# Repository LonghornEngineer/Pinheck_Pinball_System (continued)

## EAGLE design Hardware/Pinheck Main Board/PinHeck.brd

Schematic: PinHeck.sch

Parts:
3.3V, 5V, 12V, 50V: TEST_POINT_SINGLE_ROUND_100MIL; 100MIL_TP
AUDIO: SJ1-3533NS
AUX_PWR: 26-64-4040
BACK_OUT: TEST_POINT_SINGLE_ROUND_100MIL; 100MIL_TP
BATT1: 1066
BOARD_POWER_IN: 26-64-4040; 26-64-4040(KEYPIN2)
C1, C2, C3, C4, C5, C6, C7, C9, C11, C12, C20, C21, C22, C23, C24, C25, C26, C28, C30, C31, C32, C33, C37, C38, C41, C42, C45, C46, C47, C53, C54, C55, C56, C57, C62, C63, C64, C65: .1uF; 0805
C8, C36, C40, C44, C48, C52: 1uF; 0805
C10, C35, C39, C43, C51: 10uF; 1206
C13, C14: 30pF; 0805
C15, C16, C17, C18, C19: MF-CAP-12.5MM-1000uF; CP12.5MM
C27, C34, C49, C50: EEE-1VA101XP; 6.3MM_CAP_SMD
C29: MF-CAP-12.5MM-1000uF; CP6.3MM
C58, C60: 0.1uF; 0805
C59: 2.2nF; 0805
C61: 5.6nF; 0805
CABINET_I/O: 26-64-4120
CAB_RGB: 26-64-4110; 26-64-4110(KEYPIN3)
COIN_OUT: TEST_POINT_SINGLE_ROUND_100MIL; 100MIL_TP
D1: BAV99W,115; SOT-323
D2: CGRM4001-HF; SOD-123
D3: SMBJ6.0CA; SMBJ
D4: SMBJ15CA; SMBJ
D5, D6, D7, D8, D9, D10, D11: LO Q976-PS-25; LED0603
DMD_1, DMD_3, DMD_5, DMD_7, DMD_9, DMD_11, DMD_13: TEST_POINT_SINGLE_ROUND_100MIL; 100MIL_TP
DMD_CON: 5103308-2
DMD_PWR: CON_01X03_26-64-4040_(KEYPIN1); 26-64-4040(KEYPIN1)
DOOR_OUT: TEST_POINT_SINGLE_ROUND_100MIL; 100MIL_TP
ENTER_OUT: TEST_POINT_SINGLE_ROUND_100MIL; 100MIL_TP
EXT_RGB_CLK: TEST_POINT_SINGLE_ROUND_100MIL; 100MIL_TP
EXT_RGB_DATA: TEST_POINT_SINGLE_ROUND_100MIL; 100MIL_TP
F1, F2, F3, F4, F5, F6, F7: 4628
FID1, FID2, FID3: FIDUCIAL_100MIL
FID4, FID5: FIDUCIAL_0.5MM
FLASHER: 26-64-4020
GI0, GI1, GI2, GI3, GI4, GI5, GI6, GI7, GI8, GI9, GI10, GI11, GI12, GI13, GI14, GI15: TIP102; TO-220AB
GI15_: TEST_POINT_SINGLE_ROUND_100MIL; 100MIL_TP
GI_0: 26-64-4100; 26-64-4100(KEYPIN9)
GI_1: 26-64-4100; 26-64-4100(KEYPIN10)
GI_R_0, GI_R_1, GI_R_2, GI_R_3, GI_R_4, GI_R_5, GI_R_6, GI_R_7, GI_R_8, GI_R_9, GI_R_10, GI_R_11, GI_R_12, GI_R_13, GI_R_14: TEST_POINT_SINGLE_ROUND_100MIL; 100MIL_TP
GND: TEST_POINT_SINGLE_ROUND_100MIL; 100MIL_TP
H2, H3, H4, H11, H19, H21, H22, H23, H24, H26, H27, H28, H30, H31, H32, H33, H34: MOUNT_HOLE150MIL; MOUNT_HOLE_150MIL
IC2: PIC32MX795F512L-80I/PT; TQ100-PT
IC3, IC4: CD74HCT244E; DIL20
IC5: ULN2803A; DIL18
KNOCKER: 26-64-4020
LIGHT_COL: 26-64-4100; 26-64-4100(KEYPIN2)
LIGHT_C_0, LIGHT_C_1, LIGHT_C_2, LIGHT_C_3, LIGHT_C_4, LIGHT_C_5, LIGHT_C_6, LIGHT_C_7: TEST_POINT_SINGLE_ROUND_100MIL; 100MIL_TP
LIGHT_ROW: 26-64-4100; 26-64-4100(KEYPIN3)
LIGHT_R_0, LIGHT_R_1, LIGHT_R_2, LIGHT_R_3, LIGHT_R_4, LIGHT_R_5, LIGHT_R_6, LIGHT_R_7: TEST_POINT_SINGLE_ROUND_100MIL; 100MIL_TP
LOGO1: SPOOKY_LOGOSPOOKY_LOGO; SPOOKY_LOGO
L_FLIP_OUT: TEST_POINT_SINGLE_ROUND_100MIL; 100MIL_TP
OPTO_1, OPTO_2, OPTO_3, OPTO_4, OPTO_5, OPTO_6, OPTO_7: 26-64-4040
OPTO_1_, OPTO_2_, OPTO_3_, OPTO_4_, OPTO_5_, OPTO_6_, OPTO_7_: TEST_POINT_SINGLE_ROUND_100MIL; 100MIL_TP
PHABULOUS: 26-64-4050; 2.54MM_01X20_PIN_HEADER
PIC32_TC: TC2030-FTDI-TTL-232R; TC2030
PIC32_UART: CON_01X06_2.54MM_PIN_HEADER; 2.54MM_01X06_PIN_HEADER
PICKIT3: CON_01X06_2.54MM_PIN_HEADER; 2.54MM_01X06_PIN_HEADER
PICKIT3_TC: TC2030-PKT-NL; TC2030
PIC_PROGRAM: TACT_6MM; TACT6MM
PIC_RESET: TACT_6MM; TACT6MM
PROP_ACT: LG R971-KN-1; LED_0805
PROP_AUX0, PROP_AUX1: TEST_POINT_SINGLE_ROUND_100MIL; 100MIL_TP
PROP_CONFIG: TACT_6MM; TACT6MM
PROP_RESET: TACT_6MM; TACT6MM
PROP_TC: TC2030-FTDI-TTL-232R; TC2030
PROP_UART: CON_01X06_2.54MM_PIN_HEADER; 2.54MM_01X06_PIN_HEADER
PSU_PWR: LG R971-KN-1; LED_0805
R1, R4, R16, R17, R18, R19, R20, R21, R22, R23, R24, R25, R35, R36, R37, R38, R39, R40, R41, R42, R43, R44, R45, R46, R47, R48, R49, R50, R51, R52, R53, R54, R55, R56, R57, R58, R59, R60, R61, R62, R63, R64, R65, R66, R67, R68, R69, R70, R71, R72, R73, R74, R75, R76, R77, R78, R79, R80, R81, R82, R83, R85, R87, R89, R91, R93, R95, R97, R115, R119, R120, R121, R122, R123, R124, R133, R135, R137, R176: 10K; 0805
R2, R6, R9, R11, R27, R29, R33: 2K; 0805
R3, R136: 0; 0805
R5, R7, R10, R15, R28, R31, R138: 1K; 0805
R8, R139, R140, R141, R142, R143, R144, R145: 200; 0805
R12, R13, R14: 50; 0805
R26, R148, R149, R150, R151, R152, R153, R154, R155, R156: 100; 0805
R30, R84, R86, R88, R90, R92, R94, R96, R98, R99, R100, R101, R102, R103, R104, R105, R106, R107, R108, R109, R110, R111, R112, R113, R114, R116, R117, R118, R125, R126, R127, R128, R129, R130, R131, R132: 360; 0805
R32, R34: 4.7K; 0805
R134: 25K; 0805
R146: 130K; 0805
R147, R158: 1M; 0805
R157: 110K; 0805
R159, R161, R162: 180; 0805
R160: 680; 0805
R163, R164, R165: CRCW25125K60JNEG; 2512
RGB_0, RGB_1, RGB_2, RGB_3, RGB_4, RGB_5: RFP12N10L; TO-220AB
RGB_BOUT_L: TEST_POINT_SINGLE_ROUND_100MIL; 100MIL_TP
RGB_BOUT_R: TEST_POINT_SINGLE_ROUND_100MIL; 100MIL_TP
RGB_COM_OUT: 26-64-4080; 26-64-4080(KEYPIN2)
RGB_GOUT_L: TEST_POINT_SINGLE_ROUND_100MIL; 100MIL_TP
RGB_GOUT_R: TEST_POINT_SINGLE_ROUND_100MIL; 100MIL_TP
RGB_ROUT_L: TEST_POINT_SINGLE_ROUND_100MIL; 100MIL_TP
RGB_ROUT_R: TEST_POINT_SINGLE_ROUND_100MIL; 100MIL_TP
R_FLIP_OUT: TEST_POINT_SINGLE_ROUND_100MIL; 100MIL_TP
SD0: SD-RSMT-2-MQ
SD_CS: TEST_POINT_SINGLE_ROUND_100MIL; 100MIL_TP
SD_DI: TEST_POINT_SINGLE_ROUND_100MIL; 100MIL_TP
SD_DO: TEST_POINT_SINGLE_ROUND_100MIL; 100MIL_TP
SD_SCLK: TEST_POINT_SINGLE_ROUND_100MIL; 100MIL_TP
SERVO_0, SERVO_1, SERVO_2, SERVO_3, SERVO_4: 640454-3
SERVO_0_, SERVO_1_, SERVO_2_, SERVO_3_, SERVO_4_: TEST_POINT_SINGLE_ROUND_100MIL; 100MIL_TP
SHAKER: 26-64-4020
SOCKET1, SOCKET2: 820-AG11D-ESL-LF; 20PIN_DIP_SOCKET
SOCKET3, SOCKET5: 808-AG11D-ESL-LF; 8PIN_DIP_SOCKET
SOCKET4: 818-AG11D-ESL-LF; 18PIN_DIP_SOCKET
SOLENOID_POWER_IN: 26-64-4040; 26-64-4040(KEYPIN3)
SOL_0, SOL_1, SOL_2, SOL_3, SOL_4, SOL_5, SOL_6, SOL_7, SOL_8, SOL_9, SOL_10, SOL_11, SOL_12, SOL_13, SOL_14, SOL_15, SOL_16, SOL_17, SOL_18, SOL_19, SOL_20, SOL_21, SOL_22, SOL_23: IRL530PBF; TO-220AB
SOL_BANK_0: 26-64-4100; 26-64-4100(KEYPIN6)
SOL_BANK_1: 26-64-4100; 26-64-4100(KEYPIN7)
SOL_BANK_2: 26-64-4100; 26-64-4100(KEYPIN8)
SOL_GND: TEST_POINT_SINGLE_ROUND_100MIL; 100MIL_TP
SOL_PWR_0, SOL_PWR_1, SOL_PWR_2, SOL_PWR_3, SOL_PWR_4, SOL_PWR_5, SOL_PWR_6, SOL_PWR_7, SOL_PWR_8, SOL_PWR_9, SOL_PWR_10, SOL_PWR_11, SOL_PWR_12, SOL_PWR_13, SOL_PWR_14, SOL_PWR_15, SOL_PWR_16, SOL_PWR_17, SOL_PWR_18, SOL_PWR_19, SOL_PWR_20, SOL_PWR_21, SOL_PWR_22, SOL_PWR_23: TEST_POINT_SINGLE_ROUND_100MIL; 100MIL_TP
ST_BU_OUT: TEST_POINT_SINGLE_ROUND_100MIL; 100MIL_TP
ST_LI: NDP6020P; TO-220AB
ST_LI_: TEST_POINT_SINGLE_ROUND_100MIL; 100MIL_TP
SW_COL: 26-64-4100; 26-64-4100(KEYPIN5)
SW_C_0, SW_C_1, SW_C_2, SW_C_3, SW_C_4, SW_C_5, SW_C_6, SW_C_7: TEST_POINT_SINGLE_ROUND_100MIL; 100MIL_TP
SW_ROW: 26-64-4100; 26-64-4100(KEYPIN4)
SW_R_0, SW_R_1, SW_R_2, SW_R_3, SW_R_4, SW_R_5, SW_R_6, SW_R_7: TEST_POINT_SINGLE_ROUND_100MIL; 100MIL_TP
SYM1: HIGH_VOLTAGE_500MIL
S_L: TEST_POINT_SINGLE_ROUND_100MIL; 100MIL_TP
S_R: TEST_POINT_SINGLE_ROUND_100MIL; 100MIL_TP
TILT_OUT: TEST_POINT_SINGLE_ROUND_100MIL; 100MIL_TP
U1: P8X32A-Q44; P8X32A_LQFP-44
U2: DS1340Z-33+; DS1340Z_SOIC-8
U3, U5: CD74HC595M96; CD74HC595_SOIC-16
U4, U13: CAT24M01LI-G; DIP-8
U6: TPS259251; TPS2592(50/51/60/61)_VSON-10
U7: TPS259261; TPS2592(50/51/60/61)_VSON-10
U8: MF-DSC-SOT233-MMBT3904; SOT-23-3
U10: 74HCT2G04GV,125; 74HCT2G04_TTSOP-6
U11, U12: 74HC165D-Q100,118; CD74HC165_SOIC-16
U14, U15, U16, U17, U18, U19: MC74HC08ADR2G; MC74HC08_SOIC-14
U20, U21, U22, U23, U24, U25, U26, U27: TIP107; TO-220AB
U28, U29, U30, U31, U32, U33, U34, U35: TIP102; TO-220AB
U36, U38: WS2801; WS2801_SOP-14
U39: NCP1117DT33G; NCP1117DT_DPAK-3
U52: CD74HC123M96; CD74HC123_SOIC-16
U$1: LHE_LOGOLHE_LOGO; LHE_LOGO
U$2: MF_LOGOLOGO_TEXT; MF_LOGO_TEXT
USB_PROG: N/A; 2.54MM_01X04_PIN_HEADER
USER_0_OUT: TEST_POINT_SINGLE_ROUND_100MIL; 100MIL_TP
WD: LG R971-KN-1; LED_0805
X1: FQ7050B-8.000; FQ7050B
X2: 9C-6.500MAAJ-T; HC-49/US_SM
X3: ABS25-32.768KHz-1-T; 8MM_X_3.8MM

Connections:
3.3V: 3.3V.P$1, AUX_PWR.4, C2.1, C3.1, C4.1, C5.1, C6.1, C7.1, C11.1, C12.2, C15.P$1, C18.P$1, C20.2, C21.2, C22.2, C23.2, C24.2, C28.2, C31.2, C32.2, C33.2, C34.POS, C35.1, C36.1, C37.1, C46.2, C47.2, C49.POS, C54.2, C55.2, C56.1, C57.1, D1.2 (AN), IC2.2 (VDD), IC2.16 (VDD), IC2.37 (VDD), IC2.46 (VDD), IC2.55 (VUSB), IC2.62 (VDD), IC2.86 (VDD), IC3.20 (VCC), IC4.20 (VCC), OPTO_1.2, OPTO_2.2, OPTO_3.2, OPTO_4.2, OPTO_5.2, OPTO_6.2, OPTO_7.2, PHABULOUS.2, PICKIT3.2, PICKIT3_TC.P$2 (PIN2), PSU_PWR.ANODE, R1.2, R3.1, R4.2, R16.2, R17.2, R18.1, R19.1, R20.1, R21.1, R22.1, R23.1, R24.2, R25.2, R35.2, R36.2, R37.2, R38.2, R39.2, R40.2, R41.2, R42.2, R43.2, R44.2, R45.2, R46.2, R47.2, R48.2, R49.2, R50.2, R75.1, R76.1, R77.1, R78.1, R79.2, R80.2, R81.2, R82.2, R119.2, R120.2, R121.2, R122.2, R123.2, R124.2, R137.2, R176.2, SD0.4 (3.3V), U1.8 (VDD), U1.18 (VDD), U1.30 (VDD), U1.40 (VDD), U2.8 (VCC), U4.8 (VCC), U11.16 (VCC), U12.16 (VCC), U13.8 (VCC), U36.14 (VDD), U38.14 (VDD), U39.TAB (OUT)
5V: AUX_PWR.3, C16.P$1, C19.P$1, C25.2, C26.2, C30.1, C38.1, C39.1, C40.1, C41.1, C42.1, C48.1, C50.POS, C51.1, C52.1, C53.1, C62.1, C63.1, C64.1, C65.1, CABINET_I/O.P$2 (2), D2.1 (CATHODE), DMD_PWR.3 (PIN2), F4.P$1, F5.P$1, F6.P$1, PHABULOUS.3, R115.1, R134.2, R139.1, R140.1, R141.1, R142.1, R143.1, R144.1, R145.1, RGB_COM_OUT.P$7 (7), ST_LI.S (EMITTER), U3.10 (MR), U3.16 (VCC), U5.10 (MR), U5.16 (VCC), U6.P$6 (OUT), U6.P$7 (OUT), U6.P$8 (OUT), U10.5 (VCC), U14.14 (VCC), U15.14 (VCC), U16.14 (VCC), U17.14 (VCC), U18.14 (VCC), U19.14 (VCC), U39.3 (IN), U52.2 (!1B), U52.3 (!1R), U52.16 (VCC)
5V_IN: 5V.P$1, BOARD_POWER_IN.1 (PIN1), C58.1, D3.CATH (CATHODE), R147.1, U6.P$3 (VIN), U6.P$4 (VIN), U6.P$5 (VIN)
12V: AUX_PWR.2, C17.P$1, C29.P$1, C43.1, C44.1, C45.1, CAB_RGB.P$3 (3), CAB_RGB.P$7 (7), DMD_PWR.2 (PIN1), F7.P$1, PHABULOUS.7, R83.1, R85.1, R87.1, R89.1, R91.1, R93.1, R95.1, R97.1, RGB_COM_OUT.P$6 (6), U7.P$6 (OUT), U7.P$7 (OUT), U7.P$8 (OUT), U20.S (EMITTER), U21.S (EMITTER), U22.S (EMITTER), U23.S (EMITTER), U24.S (EMITTER), U25.S (EMITTER), U26.S (EMITTER), U27.S (EMITTER)
12V_IN: 12V.P$1, BOARD_POWER_IN.3 (PIN2), C60.1, D4.CATH (CATHODE), R158.1, U7.P$3 (VIN), U7.P$4 (VIN), U7.P$5 (VIN)
50V: 50V.P$1, F1.P$1, F2.P$1, F3.P$1, SOLENOID_POWER_IN.4 (PIN3)
50V_FUSE_0: D9.ANODE, F1.P$2, KNOCKER.P$1 (PIN1), SHAKER.P$1 (PIN1), SOL_BANK_0.P$1 (PIN1)
50V_FUSE_1: D10.ANODE, F2.P$2, SOL_BANK_1.P$1 (PIN1)
50V_FUSE_2: D11.ANODE, F3.P$2, SOL_BANK_2.P$1 (PIN1)
!DATA_LAT: U3.12 (STCP), U5.12 (STCP), U10.6 (1Y)
AUD0: R32.1, U1.16 (P15)
AUD1: R34.1, U1.15 (P14)
AUX_0: R35.1, R138.1, U11.11 (D0)
AUX_1: R31.1, R36.1, U11.12 (D1)
AUX_2: R28.1, R37.1, U11.13 (D2)
AUX_3: R15.1, R39.1, U11.3 (D4)
AUX_4: R10.1, R40.1, U11.4 (D5)
AUX_5: R7.1, R41.1, U11.5 (D6)
AUX_6: R5.1, R42.1, U11.6 (D7)
AVCC: C8.1, C9.1, IC2.30 (AVDD), R3.2
BACK: R47.1, R152.2, U12.3 (D4)
BACK_OUT: BACK_OUT.P$1, CABINET_I/O.P$8 (8), R152.1
BKUP_V: BATT1.POS (+), U2.3 (V_BACK)
CAB_CLK: IC2.93 (PMD0/RE0), U3.11 (SHCP), U5.11 (SHCP), U11.2 (CLK), U12.2 (CLK)
CAB_GI_OUT: IC2.11 (ECRS/SDA2A/SDI2A/U2ARX/PMA4/CN9/RG7), U3.14 (DS)
CAB_LAT: IC2.12 (SCL2A/SDO2A/U2ATX/PMA3/CN10/RG8), U10.1 (1A), U11.1 (LAT), U12.1 (LAT)
CAB_SWITCH_IN: IC2.87 (C1RX/ETXD1/PMD11/RF0), U11.9 (QH)
COIN: R49.1, R150.2, U12.5 (D6)
COIN_OUT: CABINET_I/O.P$6 (6), COIN_OUT.P$1, R150.1
COMM_CLK_RX: IC2.40 (AC1RX/SS3A/U3BRX/U3ACTS/RF12), U1.32 (P25)
COMM_IN_TX: IC2.39 (AC1TX/SCK3A/U3BTX/U3ARTS/RF13), U1.31 (P24)
COMM_OUT: IC2.50 (SCL3A/SDO3A/U3ATX/PMA8/CN18/RF5), U1.33 (P26)
DATA_CAB1: U11.10 (SER), U12.9 (QH)
DMD_1: DMD_1.P$1, DMD_CON.1 (PIN1), U1.25 (P22)
DMD_3: DMD_3.P$1, DMD_CON.3 (PIN3), U1.24 (P21)
DMD_5: DMD_5.P$1, DMD_CON.5 (PIN5), U1.23 (P20)
DMD_7: DMD_7.P$1, DMD_CON.7 (PIN7), U1.22 (P19)
DMD_9: DMD_9.P$1, DMD_CON.9 (PIN9), U1.21 (P18)
DMD_11: DMD_11.P$1, DMD_CON.11 (PIN11), U1.20 (P17)
DMD_13: DMD_13.P$1, DMD_CON.13 (PIN13), U1.19 (P16)
DOOR: R43.1, R153.2, U12.11 (D0)
DOOR_OUT: CABINET_I/O.P$9 (9), DOOR_OUT.P$1, R153.1
ENTER: R48.1, R151.2, U12.4 (D5)
ENTER_OUT: CABINET_I/O.P$7 (7), ENTER_OUT.P$1, R151.1
EXT_RGB_CLK: EXT_RGB_CLK.P$1, IC2.6 (T2CK/RC1), RGB_COM_OUT.P$5 (5)
EXT_RGB_DATA: EXT_RGB_DATA.P$1, IC2.10 (ECOL/SCK2A/U2BTXU2ARTS/PMA5/CN8/RG6), RGB_COM_OUT.P$4 (4)
FLASH_12V: D6.ANODE, F7.P$2, FLASHER.P$1 (PIN1)
GI0_5V: D7.ANODE, F5.P$2, GI_0.P$10 (PIN9)
GI1_5V: D8.ANODE, F4.P$2, GI_1.P$9 (PIN9)
GI15: GI15.D (COLLECTOR), GI15_.P$1, GI_1.P$8 (PIN8)
GI_0: R99.1, U3.15 (Q0)
GI_1: R101.1, U3.1 (Q1)
GI_2: R103.1, U3.2 (Q2)
GI_3: R105.1, U3.3 (Q3)
GI_4: R107.1, U3.4 (Q4)
GI_5: R109.1, U3.5 (Q5)
GI_6: R111.1, U3.6 (Q6)
GI_7: R113.1, U3.7 (Q7)
GI_8: R125.1, U5.15 (Q0)
GI_9: R126.1, U5.1 (Q1)
GI_10: R127.1, U5.2 (Q2)
GI_11: R128.1, U5.3 (Q3)
GI_12: R129.1, U5.4 (Q4)
GI_13: R130.1, U5.5 (Q5)
GI_14: R131.1, U5.6 (Q6)
GI_15: R132.1, U5.7 (Q7)
GI_DATA_COL_B: U3.9 (Q7S), U5.14 (DS)
GI_R_0: GI0.D (COLLECTOR), GI_0.P$1 (PIN1), GI_R_0.P$1
GI_R_1: GI1.D (COLLECTOR), GI_0.P$2 (PIN2), GI_R_1.P$1
GI_R_2: GI2.D (COLLECTOR), GI_0.P$3 (PIN3), GI_R_2.P$1
GI_R_3: GI3.D (COLLECTOR), GI_0.P$4 (PIN4), GI_R_3.P$1
GI_R_4: GI4.D (COLLECTOR), GI_0.P$5 (PIN5), GI_R_4.P$1
GI_R_5: GI5.D (COLLECTOR), GI_0.P$6 (PIN6), GI_R_5.P$1
GI_R_6: GI6.D (COLLECTOR), GI_0.P$7 (PIN7), GI_R_6.P$1
GI_R_7: GI7.D (COLLECTOR), GI_0.P$8 (PIN8), GI_R_7.P$1
GI_R_8: GI8.D (COLLECTOR), GI_1.P$1 (PIN1), GI_R_8.P$1
GI_R_9: GI9.D (COLLECTOR), GI_1.P$2 (PIN2), GI_R_9.P$1
GI_R_10: GI10.D (COLLECTOR), GI_1.P$3 (PIN3), GI_R_10.P$1
GI_R_11: GI11.D (COLLECTOR), GI_1.P$4 (PIN4), GI_R_11.P$1
GI_R_12: GI12.D (COLLECTOR), GI_1.P$5 (PIN5), GI_R_12.P$1
GI_R_13: GI13.D (COLLECTOR), GI_1.P$6 (PIN6), GI_R_13.P$1
GI_R_14: GI14.D (COLLECTOR), GI_1.P$7 (PIN7), GI_R_14.P$1
GND: AUDIO.1_A (S), AUDIO.1_B (S), AUDIO.S1 (SHIELD), AUDIO.S2 (SHIELD), AUDIO.S3 (SHIELD), AUDIO.S4 (SHIELD), AUDIO.S5 (SHIELD), AUDIO.S6 (SHIELD), AUX_PWR.1, BATT1.NEG (-), BOARD_POWER_IN.4 (PIN3), C2.2, C3.2, C4.2, C5.2, C6.2, C7.2, C8.2, C9.2, C10.2, C11.2, C12.1, C13.2, C14.2, C15.P$2, C16.P$2, C17.P$2, C18.P$2, C19.P$2, C20.1, C21.1, C22.1, C23.1, C24.1, C25.1, C26.1, C27.NEG, C28.1, C29.P$2, C30.2, C31.1, C32.1, C33.1, C34.NEG, C35.2, C36.2, C37.2, C38.2, C39.2, C40.2, C41.2, C42.2, C43.2, C44.2, C45.2, C46.1, C47.1, C48.2, C49.NEG, C50.NEG, C51.2, C52.2, C53.2, C54.1, C55.1, C56.2, C57.2, C58.2, C59.2, C60.2, C61.2, C62.2, C63.2, C64.2, C65.2, CABINET_I/O.P$1 (1), D1.1 (CAT), D3.ANODE, D4.ANODE, DMD_CON.2 (PIN2), DMD_CON.4 (PIN4), DMD_CON.6 (PIN6), DMD_CON.8 (PIN8), DMD_CON.10 (PIN10), DMD_CON.12 (PIN12), DMD_CON.14 (PIN14), DMD_PWR.4 (PIN3), FLASHER.P$2 (PIN2), GI0.S (EMITTER), GI1.S (EMITTER), GI2.S (EMITTER), GI3.S (EMITTER), GI4.S (EMITTER), GI5.S (EMITTER), GI6.S (EMITTER), GI7.S (EMITTER), GI8.S (EMITTER), GI9.S (EMITTER), GI10.S (EMITTER), GI11.S (EMITTER), GI12.S (EMITTER), GI13.S (EMITTER), GI14.S (EMITTER), GI15.S (EMITTER), GND.P$1, IC2.15 (VSS), IC2.31 (AVSS), IC2.36 (VSS), IC2.45 (VSS), IC2.65 (VSS), IC2.75 (VSS), IC3.1 (G), IC3.10 (GND), IC3.19 (G), IC4.1 (G), IC4.10 (GND), IC4.19 (G), IC5.9 (GND), OPTO_1.3, OPTO_2.3, OPTO_3.3, OPTO_4.3, OPTO_5.3, OPTO_6.3, OPTO_7.3, PHABULOUS.1, PHABULOUS.6, PHABULOUS.8, PHABULOUS.11, PIC32_TC.P$5 (PIN5), PIC32_UART.1, PICKIT3.3, PICKIT3_TC.P$3 (PIN3), PIC_PROGRAM.P$4, PIC_RESET.P$1, PROP_CONFIG.P$4, PROP_RESET.P$3, PROP_TC.P$5 (PIN5), PROP_UART.1, R2.1, R6.1, R9.1, R11.1, R27.1, R29.1, R30.1, R33.1, R51.1, R52.1, R53.1, R54.1, R55.1, R56.1, R57.1, R58.1, R59.1, R60.1, R61.1, R62.1, R63.1, R64.1, R65.1, R66.1, R67.1, R68.1, R69.1, R70.1, R71.1, R72.1, R73.1, R74.1, R117.1, R118.2, R133.2, R135.2, R136.1, R146.2, R157.2, R159.2, R160.2, R161.2, R162.2, RGB_0.S (SOURCE), RGB_1.S (SOURCE), RGB_2.S (SOURCE), RGB_3.S (SOURCE), RGB_4.S (SOURCE), RGB_5.S (SOURCE), RGB_COM_OUT.P$1 (1), SD0.3 (GND), SD0.6 (GND), SD0.GND_1 (GND), SD0.GND_2 (GND), SERVO_0.P$1 (PIN1), SERVO_1.P$1 (PIN1), SERVO_2.P$1 (PIN1), SERVO_3.P$1 (PIN1), SERVO_4.P$1 (PIN1), U1.5 (VSS), U1.6 (!BOE), U1.17 (VSS), U1.27 (VSS), U1.39 (VSS), U2.4 (VSS), U3.8 (GND), U3.13 (OE), U4.2 (A1), U4.3 (A2), U4.4 (GND), U4.7 (WP), U5.8 (GND), U5.13 (OE), U6.P$9 (GND), U6.PAD (GND), U6.PAD2 (GND), U6.PAD3 (GND), U6.PAD4 (GND), U6.PAD5 (GND), U6.PAD6 (GND), U6.PAD7 (GND), U7.P$9 (GND), U7.PAD (GND), U7.PAD2 (GND), U7.PAD3 (GND), U7.PAD4 (GND), U7.PAD5 (GND), U7.PAD6 (GND), U7.PAD7 (GND), U8.P$2 (EMITTER), U10.2 (GND), U11.8 (GND), U11.15 (C_INH), U12.8 (GND), U12.15 (C_INH), U13.2 (A1), U13.3 (A2), U13.4 (GND), U13.7 (WP), U14.7 (GND), U15.7 (GND), U16.7 (GND), U17.7 (GND), U18.7 (GND), U19.7 (GND), U28.S (EMITTER), U29.S (EMITTER), U30.S (EMITTER), U31.S (EMITTER), U32.S (EMITTER), U33.S (EMITTER), U34.S (EMITTER), U35.S (EMITTER), U36.3 (POL), U36.4 (RFB), U36.5 (GFB), U36.6 (BFB), U36.7 (GND)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
I2C_SCL: IC2.66 (AETXCLK/SCL1/INT3/RA14), PHABULOUS.5, R24.1, U2.6 (SCL), U13.6 (SCL)
I2C_SDA: IC2.67 (AETXEN/SDA1/INT4/RA15), PHABULOUS.4, R25.1, U2.5 (SDA), U13.5 (SDA)
LIGHT_C_0: LIGHT_COL.P$3 (PIN2), LIGHT_C_0.P$1, U20.D (COLLECTOR)
LIGHT_C_1: LIGHT_COL.P$4 (PIN3), LIGHT_C_1.P$1, U21.D (COLLECTOR)
LIGHT_C_2: LIGHT_COL.P$5 (PIN4), LIGHT_C_2.P$1, U22.D (COLLECTOR)
LIGHT_C_3: LIGHT_COL.P$6 (PIN5), LIGHT_C_3.P$1, U23.D (COLLECTOR)
LIGHT_C_4: LIGHT_COL.P$7 (PIN6), LIGHT_C_4.P$1, U24.D (COLLECTOR)
LIGHT_C_5: LIGHT_COL.P$8 (PIN7), LIGHT_C_5.P$1, U25.D (COLLECTOR)
LIGHT_C_6: LIGHT_COL.P$9 (PIN8), LIGHT_C_6.P$1, U26.D (COLLECTOR)
LIGHT_C_7: LIGHT_COL.P$10 (PIN9), LIGHT_C_7.P$1, U27.D (COLLECTOR)
LIGHT_C_B_0: R83.2, R84.2, U20.G (BASE)
LIGHT_C_B_1: R85.2, R86.2, U21.G (BASE)
LIGHT_C_B_2: R87.2, R88.2, U22.G (BASE)
LIGHT_C_B_3: R89.2, R90.2, U23.G (BASE)
LIGHT_C_B_4: R91.2, R92.2, U24.G (BASE)
LIGHT_C_B_5: R93.2, R94.2, U25.G (BASE)
LIGHT_C_B_6: R95.2, R96.2, U26.G (BASE)
LIGHT_C_B_7: R97.2, R98.2, U27.G (BASE)
LIGHT_DTA_0: IC5.11 (O8), R84.1
LIGHT_DTA_1: IC5.12 (O7), R86.1
LIGHT_DTA_2: IC5.13 (O6), R88.1
LIGHT_DTA_3: IC5.14 (O5), R90.1
LIGHT_DTA_4: IC5.15 (O4), R92.1
LIGHT_DTA_5: IC5.16 (O3), R94.1
LIGHT_DTA_6: IC5.17 (O2), R96.1
LIGHT_DTA_7: IC5.18 (O1), R98.1
LIGHT_R_0: LIGHT_ROW.P$2 (PIN2), LIGHT_R_0.P$1, U28.D (COLLECTOR)
LIGHT_R_1: LIGHT_ROW.P$4 (PIN3), LIGHT_R_1.P$1, U29.D (COLLECTOR)
LIGHT_R_2: LIGHT_ROW.P$5 (PIN4), LIGHT_R_2.P$1, U30.D (COLLECTOR)
LIGHT_R_3: LIGHT_ROW.P$6 (PIN5), LIGHT_R_3.P$1, U31.D (COLLECTOR)
LIGHT_R_4: LIGHT_ROW.P$7 (PIN6), LIGHT_R_4.P$1, U32.D (COLLECTOR)
LIGHT_R_5: LIGHT_ROW.P$8 (PIN7), LIGHT_R_5.P$1, U33.D (COLLECTOR)
LIGHT_R_6: LIGHT_ROW.P$9 (PIN8), LIGHT_R_6.P$1, U34.D (COLLECTOR)
LIGHT_R_7: LIGHT_ROW.P$10 (PIN9), LIGHT_R_7.P$1, U35.D (COLLECTOR)
L_FLIP: R46.1, R156.2, U12.14 (D3)
L_FLIP_OUT: CABINET_I/O.P$12 (12), L_FLIP_OUT.P$1, R156.1
unnamed: U2.2 (X2), X3.4
unnamed: U2.1 (X1), X3.1
unnamed: PROP_ACT.CATHODE, R30.2
unnamed: C1.1, PROP_TC.P$6 (PIN6), PROP_UART.6
unnamed: C10.1, IC2.85 (VCAP/VDDCORE)
unnamed: OPTO_6.4, R144.2
unnamed: OPTO_5.4, R143.2
unnamed: OPTO_1.4, R139.2
unnamed: PIC_RESET.P$4, R8.1
unnamed: OPTO_7.4, R145.2
unnamed: OPTO_4.4, R142.2
unnamed: OPTO_3.4, R141.2
unnamed: R100.2, U28.G (BASE)
unnamed: OPTO_2.4, R140.2
unnamed: R102.2, U29.G (BASE)
unnamed: R147.2, U6.P$2 (EN/UVLO)
unnamed: R158.2, U7.P$2 (EN/UVLO)
unnamed: D5.CATHODE, R159.1
unnamed: R23.2, SD0.9 (RW)
unnamed: PIC32_TC.P$6 (PIN6), PIC32_UART.6, R26.1
unnamed: R104.2, U30.G (BASE)
unnamed: R119.1, RGB_0.G (GATE), U38.8 (BOUT)
unnamed: R120.1, RGB_1.G (GATE), U38.9 (GOUT)
unnamed: D6.CATHODE, R160.1
unnamed: R121.1, RGB_2.G (GATE), U38.10 (ROUT)
unnamed: R124.1, RGB_5.G (GATE), U36.10 (ROUT)
unnamed: D7.CATHODE, R161.1
unnamed: R123.1, RGB_4.G (GATE), U36.9 (GOUT)
unnamed: R122.1, RGB_3.G (GATE), U36.8 (BOUT)
unnamed: D8.CATHODE, R162.1
unnamed: PICKIT3.4, PICKIT3_TC.P$4 (PIN4), R13.2
unnamed: R116.1, U8.P$1 (BASE)
unnamed: PICKIT3.5, PICKIT3_TC.P$5 (PIN5), R14.2
unnamed: R106.2, U31.G (BASE)
unnamed: C13.1, IC2.64 (OSC2/CLKO/RC15), X1.1
unnamed: D1.3 (COM), IC2.13 (MCLR), R12.1
unnamed: D9.CATHODE, R163.1
unnamed: R108.2, U32.G (BASE)
unnamed: C14.1, IC2.63 (OSC1/CLKI/RC12), X1.3 (2)
unnamed: D10.CATHODE, R164.1
unnamed: R110.2, U33.G (BASE)
unnamed: R112.2, U34.G (BASE)
unnamed: D11.CATHODE, R165.1
unnamed: R114.2, U35.G (BASE)
unnamed: R146.1, U6.P$10 (ILIM)
unnamed: R115.2, ST_LI.G (BASE), U8.P$3 (COLLECTOR)
unnamed: R118.1, WD.CATHODE
unnamed: PSU_PWR.CATHODE, R117.2
unnamed: C59.1, U6.P$1 (DV/DT)
unnamed: C61.1, U7.P$1 (DV/DT)
unnamed: R157.1, U7.P$10 (ILIM)
unnamed: GI0.G (BASE), R99.2
unnamed: GI1.G (BASE), R101.2
unnamed: GI2.G (BASE), R103.2
unnamed: GI3.G (BASE), R105.2
unnamed: GI4.G (BASE), R107.2
unnamed: GI5.G (BASE), R109.2
unnamed: GI6.G (BASE), R111.2
unnamed: GI7.G (BASE), R113.2
unnamed: GI8.G (BASE), R125.2
unnamed: GI9.G (BASE), R126.2
unnamed: GI10.G (BASE), R127.2
unnamed: GI11.G (BASE), R128.2
unnamed: GI12.G (BASE), R129.2
unnamed: GI13.G (BASE), R130.2
unnamed: GI14.G (BASE), R131.2
unnamed: GI15.G (BASE), R132.2
OPTO_1: OPTO_1.1, OPTO_1_.P$1, R2.2, R5.2
OPTO_2: OPTO_2.1, OPTO_2_.P$1, R6.2, R7.2
OPTO_3: OPTO_3.1, OPTO_3_.P$1, R9.2, R10.2
OPTO_4: OPTO_4.1, OPTO_4_.P$1, R11.2, R15.2
OPTO_5: OPTO_5.1, OPTO_5_.P$1, R27.2, R28.2
OPTO_6: OPTO_6.1, OPTO_6_.P$1, R29.2, R31.2
OPTO_7: OPTO_7.1, OPTO_7_.P$1, R33.2, R138.2
P32_MCLR: PICKIT3.1, PICKIT3_TC.P$1 (PIN1), R4.1, R8.2, R12.2, R26.2
PIC_ENABLE: IC2.1 (AERXERR/RG15), R133.1, U52.1 (!1A)
PIC_LIGHT_C_0: IC2.25 (PGED1/AN0/CN2/RB0), IC5.8 (I8)
PIC_LIGHT_C_1: IC2.24 (PGEC1/AN1/CN3/RB1), IC5.7 (I7)
PIC_LIGHT_C_2: IC2.23 (AN2/C2IN-/CN4/RB2), IC5.6 (I6)
PIC_LIGHT_C_3: IC2.22 (AN3/C2IN+/CN5/RB3), IC5.5 (I5)
PIC_LIGHT_C_4: IC2.21 (AN4/C1IN-/CN6/RB4), IC5.4 (I4)
PIC_LIGHT_C_5: IC2.20 (AN5/C1IN+/VBUSON/CN7/RB5), IC5.3 (I3)
PIC_LIGHT_C_6: IC2.26 (PGEC2/AN6/OCFA/RB6), IC5.2 (I2), R14.1
PIC_LIGHT_C_7: IC2.27 (PGED2/AN7/RB7), IC5.1 (I1), R13.1
PIC_LIGHT_R_0: IC2.32 (AN8/C1OUT/RB8), R100.1
PIC_LIGHT_R_1: IC2.33 (AN9/C2OUT/RB9), R102.1
PIC_LIGHT_R_2: IC2.34 (AN10/CVREFOUT/PMA13/RB10), R104.1
PIC_LIGHT_R_3: IC2.35 (AN11/ERXERR/AETXERR/PMA12/RB11), R106.1
PIC_LIGHT_R_4: IC2.41 (AN12/ERXD0/AECRS/PMA11/RB12), R108.1
PIC_LIGHT_R_5: IC2.42 (AN13/ERXD1/AECOL/PMA10/RB13), R110.1
PIC_LIGHT_R_6: IC2.43 (AN14/ERXD2/AETXD3/PMALH/PMA1/RB14), R112.1
PIC_LIGHT_R_7: IC2.44 (OCFB/PMALL/PMA0/CN12/RB15), R114.1
PIC_PROGRAM_SW: IC2.14 (SS2A/U2BRX/U2ACTS/PMA2/CN11/RG9), PIC_PROGRAM.P$1, R137.1
PIC_SOL_0: IC2.7 (T3CK/AC2TX/RC2), R58.2, U14.2 (B1)
PIC_SOL_1: IC2.8 (T4CK/AC2RX/RC3), R57.2, U14.5 (B2)
PIC_SOL_2: IC2.3 (PMD5/RE5), R56.2, U14.10 (B3)
PIC_SOL_3: IC2.51 (USBID/RF3), R55.2, U14.13 (B4)
PIC_SOL_4: IC2.4 (PMD6/RE6), R54.2, U17.2 (B1)
PIC_SOL_5: IC2.5 (PMD7/RE7), R53.2, U17.5 (B2)
PIC_SOL_6: IC2.18 (AERXD0/INT1/RE8), R52.2, U17.10 (B3)
PIC_SOL_7: IC2.74 (SOSCO/T1CK/CN0/RC14), R51.2, U17.13 (B4)
PIC_SOL_8: IC2.19 (AERXD1/INT2/RE9), R66.2, U15.2 (B1)
PIC_SOL_9: IC2.9 (T5CK/SDI1/RC4), R65.2, U15.5 (B2)
PIC_SOL_10: IC2.58 (SCL2/RA2), R64.2, U15.10 (B3)
PIC_SOL_11: IC2.17 (TMS/RA0), R63.2, U15.13 (B4)
PIC_SOL_12: IC2.38 (TCK/RA1), R62.2, U18.2 (B1)
PIC_SOL_13: IC2.60 (TDI/RA4), R61.2, U18.5 (B2)
PIC_SOL_14: IC2.61 (TDO/RA5), R60.2, U18.10 (B3)
PIC_SOL_15: IC2.73 (SOSCI/CN1/RC13), R59.2, U18.13 (B4)
PIC_SOL_16: IC2.89 (C2TX/ETXERR/PMD9/RG1), R74.2, U16.2 (B1)
PIC_SOL_17: IC2.90 (C2RX/PMD8/RG0), R73.2, U16.5 (B2)
PIC_SOL_18: IC2.91 (TRCLK/RA6), R72.2, U16.10 (B3)
PIC_SOL_19: IC2.92 (TRD3/RA7), R71.2, U16.13 (B4)
PIC_SOL_20: IC2.95 (TRD2/RG14), R70.2, U19.2 (B1)
PIC_SOL_21: IC2.96 (TRD1/RG12), R69.2, U19.5 (B2)
PIC_SOL_22: IC2.97 (TRD0/RG13), R68.2, U19.10 (B3)
PIC_SOL_23: IC2.28 (VREF-/CVREF-/AERXD2/PMA7/RA9), R67.2, U19.13 (B4)
PIC_SW_C_0: IC2.68 (RTCC/EMDIO/AEMDIO/IC1/RD8), IC4.2 (A1)
PIC_SW_C_1: IC2.69 (SS1/IC2/RD9), IC4.17 (A4)
PIC_SW_C_2: IC2.70 (SCK1/IC3/PMCS2/PMA15/RD10), IC4.4 (A2)
PIC_SW_C_3: IC2.71 (EMDC/AEMDC/IC4/PMCS1/PMA14/RD11), IC4.15 (A3)
PIC_SW_C_4: IC2.79 (ETXD2/IC5/PMD12/RD12), IC4.6 (A3)
PIC_SW_C_5: IC2.80 (ETXD3/PMD13/CN19/RD13), IC4.13 (A2)
PIC_SW_C_6: IC2.47 (AETXD0/SS1A/U1BRX/U1ACTS/CN20/RD14), IC4.8 (A4)
PIC_SW_C_7: IC2.48 (AETXD1/SCK1A/U1BTX/U1ARTS/CN21/RD15), IC4.11 (A1)
PIC_SW_R_0: IC2.72 (SDO1/OC1/INT0/RD0), IC3.18 (Y1)
PIC_SW_R_1: IC2.76 (OC2/RD1), IC3.3 (Y4)
PIC_SW_R_2: IC2.77 (OC3/RD2), IC3.16 (Y2)
PIC_SW_R_3: IC2.78 (OC4/RD3), IC3.5 (Y3)
PIC_SW_R_4: IC2.81 (OC5/PMWR/CN13/RD4), IC3.14 (Y3)
PIC_SW_R_5: IC2.82 (PMRD/CN14/RD5), IC3.7 (Y2)
PIC_SW_R_6: IC2.83 (ETXEN/PMD14/CN15/RD6), IC3.12 (Y4)
PIC_SW_R_7: IC2.84 (ETXCLK/PMD15/CN16/RD7), IC3.9 (Y1)
PROP_ACT: PROP_ACT.ANODE, U1.34 (P27)
PROP_AUX0: PROP_AUX0.P$1, RGB_COM_OUT.P$3 (3), U1.1 (P4)
PROP_AUX1: PROP_AUX1.P$1, RGB_COM_OUT.P$2 (2), U1.2 (P5)
PROP_AUX2: PHABULOUS.12, U1.3 (P6)
PROP_AUX3: PHABULOUS.13, U1.4 (P7)
PROP_AUX4: PHABULOUS.14, U1.9 (P8)
PROP_AUX5: PHABULOUS.15, U1.10 (P9)
PROP_AUX6: PHABULOUS.16, U1.11 (P10)
PROP_AUX7: PHABULOUS.17, U1.12 (P11)
PROP_AUX8: PHABULOUS.18, U1.13 (P12)
PROP_AUX9: PHABULOUS.19, U1.26 (P23)
PROP_PROGRAM: PROP_CONFIG.P$1, R1.1, U1.14 (P13)
RES: C1.2, PROP_RESET.P$2, R176.1, U1.7 (!RES)
RGB_BOUT_L: CAB_RGB.P$4 (4), RGB_0.D (DRAIN), RGB_BOUT_L.P$1
RGB_BOUT_R: CAB_RGB.P$8 (8), RGB_3.D (DRAIN), RGB_BOUT_R.P$1
RGB_CLK: IC2.98 (PMD2/RE2), U38.1 (CLI)
RGB_CLK_1: U36.1 (CLI), U38.13 (CKO)
RGB_CLK_OUT: U36.13 (CKO)
RGB_DATA: IC2.94 (PMD1/RE1), U38.2 (SDI)
RGB_DATA_1: U36.2 (SDI), U38.12 (SDO)
RGB_DATA_OUT: U36.12 (SDO)
RGB_GOUT_L: CAB_RGB.P$5 (5), RGB_1.D (DRAIN), RGB_GOUT_L.P$1
RGB_GOUT_R: CAB_RGB.P$9 (9), RGB_4.D (DRAIN), RGB_GOUT_R.P$1
RGB_ROUT_L: CAB_RGB.P$6 (6), RGB_2.D (DRAIN), RGB_ROUT_L.P$1
RGB_ROUT_R: CAB_RGB.P$10 (10), RGB_5.D (DRAIN), RGB_ROUT_R.P$1
RX_PIC32: IC2.52 (SDA1A/SDI1A/U1ARX/RF2), PIC32_TC.P$4 (PIN4), PIC32_UART.4
RX_PROP: PROP_TC.P$4 (PIN4), PROP_UART.4, U1.38 (P31)
R_FLIP: R45.1, R155.2, U12.13 (D2)
R_FLIP_OUT: CABINET_I/O.P$11 (11), R155.1, R_FLIP_OUT.P$1
SCL_PROP: R16.1, U1.35 (P28), U4.6 (SCL)
SDA_PROP: R17.1, U1.36 (P29), U4.5 (SDA)
SD_CS: R22.2, SD0.1 (CS), SD_CS.P$1, U1.44 (P3)
SD_DI: R18.2, SD0.2 (DI), SD_DI.P$1, U1.43 (P2)
SD_DO: R20.2, SD0.7 (D0), SD_DO.P$1, U1.41 (P0)
SD_IQ: R21.2, SD0.8 (IRQ)
SD_SCLK: R19.2, SD0.5 (SCLK), SD_SCLK.P$1, U1.42 (P1)
SERVO_0: IC2.88 (C1TX/ETXD0/PMD10/RF1), SERVO_0.P$3 (PIN3), SERVO_0_.P$1
SERVO_1: IC2.29 (VREF+/CVREF+/AERXD3/PMA6/RA10), SERVO_1.P$3 (PIN3), SERVO_1_.P$1
SERVO_2: IC2.49 (SDA3A/SDI3A/U3ARX/PMA9/CN17/RF4), SERVO_2.P$3 (PIN3), SERVO_2_.P$1
SERVO_3: IC2.99 (PMD3/RE3), PHABULOUS.9, SERVO_3.P$3 (PIN3), SERVO_3_.P$1
SERVO_4: IC2.100 (PMD4/RE4), PHABULOUS.10, SERVO_4.P$3 (PIN3), SERVO_4_.P$1
SERVO_5V: D5.ANODE, F6.P$2, SERVO_0.P$2 (PIN2), SERVO_1.P$2 (PIN2), SERVO_2.P$2 (PIN2), SERVO_3.P$2 (PIN2), SERVO_4.P$2 (PIN2)
SOL_0: SOL_0.G (GATE), U14.3 (Y1)
SOL_1: SOL_1.G (GATE), U14.6 (Y2)
SOL_2: SOL_2.G (GATE), U14.8 (Y3)
SOL_3: SOL_3.G (GATE), U14.11 (Y4)
SOL_4: SOL_4.G (GATE), U17.3 (Y1)
SOL_5: SOL_5.G (GATE), U17.6 (Y2)
SOL_6: SOL_6.G (GATE), U17.8 (Y3)
SOL_7: SOL_7.G (GATE), U17.11 (Y4)
SOL_8: SOL_8.G (GATE), U15.3 (Y1)
SOL_9: SOL_9.G (GATE), U15.6 (Y2)
SOL_10: SOL_10.G (GATE), U15.8 (Y3)
SOL_11: SOL_11.G (GATE), U15.11 (Y4)
SOL_12: SOL_12.G (GATE), U18.3 (Y1)
SOL_13: SOL_13.G (GATE), U18.6 (Y2)
SOL_14: SOL_14.G (GATE), U18.8 (Y3)
SOL_15: SOL_15.G (GATE), U18.11 (Y4)
SOL_16: SOL_16.G (GATE), U16.3 (Y1)
SOL_17: SOL_17.G (GATE), U16.6 (Y2)
SOL_18: SOL_18.G (GATE), U16.8 (Y3)
SOL_19: SOL_19.G (GATE), U16.11 (Y4)
SOL_20: SOL_20.G (GATE), U19.3 (Y1)
SOL_21: SOL_21.G (GATE), U19.6 (Y2)
SOL_22: SOL_22.G (GATE), U19.8 (Y3)
SOL_23: SOL_23.G (GATE), U19.11 (Y4)
SOL_GND: R136.2, R163.2, R164.2, R165.2, SOLENOID_POWER_IN.1 (PIN1), SOLENOID_POWER_IN.2 (PIN2), SOL_0.S (SOURCE), SOL_1.S (SOURCE), SOL_2.S (SOURCE), SOL_3.S (SOURCE), SOL_4.S (SOURCE), SOL_5.S (SOURCE), SOL_6.S (SOURCE), SOL_7.S (SOURCE), SOL_8.S (SOURCE), SOL_9.S (SOURCE), SOL_10.S (SOURCE), SOL_11.S (SOURCE), SOL_12.S (SOURCE), SOL_13.S (SOURCE), SOL_14.S (SOURCE), SOL_15.S (SOURCE), SOL_16.S (SOURCE), SOL_17.S (SOURCE), SOL_18.S (SOURCE), SOL_19.S (SOURCE), SOL_20.S (SOURCE), SOL_21.S (SOURCE), SOL_22.S (SOURCE), SOL_23.S (SOURCE), SOL_GND.P$1
SOL_PWR_0: KNOCKER.P$2 (PIN2), SOL_0.D (DRAIN), SOL_BANK_0.P$2 (PIN2), SOL_PWR_0.P$1
SOL_PWR_1: SHAKER.P$2 (PIN2), SOL_1.D (DRAIN), SOL_BANK_0.P$3 (PIN3), SOL_PWR_1.P$1
SOL_PWR_2: SOL_2.D (DRAIN), SOL_BANK_0.P$4 (PIN4), SOL_PWR_2.P$1
SOL_PWR_3: SOL_3.D (DRAIN), SOL_BANK_0.P$5 (PIN5), SOL_PWR_3.P$1
SOL_PWR_4: SOL_4.D (DRAIN), SOL_BANK_0.P$7 (PIN6), SOL_PWR_4.P$1
SOL_PWR_5: SOL_5.D (DRAIN), SOL_BANK_0.P$8 (PIN7), SOL_PWR_5.P$1
SOL_PWR_6: SOL_6.D (DRAIN), SOL_BANK_0.P$9 (PIN8), SOL_PWR_6.P$1
SOL_PWR_7: SOL_7.D (DRAIN), SOL_BANK_0.P$10 (PIN9), SOL_PWR_7.P$1
SOL_PWR_8: SOL_8.D (DRAIN), SOL_BANK_1.P$2 (PIN2), SOL_PWR_8.P$1
SOL_PWR_9: SOL_9.D (DRAIN), SOL_BANK_1.P$3 (PIN3), SOL_PWR_9.P$1
SOL_PWR_10: SOL_10.D (DRAIN), SOL_BANK_1.P$4 (PIN4), SOL_PWR_10.P$1
SOL_PWR_11: SOL_11.D (DRAIN), SOL_BANK_1.P$5 (PIN5), SOL_PWR_11.P$1
SOL_PWR_12: SOL_12.D (DRAIN), SOL_BANK_1.P$6 (PIN6), SOL_PWR_12.P$1
SOL_PWR_13: SOL_13.D (DRAIN), SOL_BANK_1.P$8 (PIN7), SOL_PWR_13.P$1
SOL_PWR_14: SOL_14.D (DRAIN), SOL_BANK_1.P$9 (PIN8), SOL_PWR_14.P$1
SOL_PWR_15: SOL_15.D (DRAIN), SOL_BANK_1.P$10 (PIN9), SOL_PWR_15.P$1
SOL_PWR_16: SOL_16.D (DRAIN), SOL_BANK_2.P$2 (PIN2), SOL_PWR_16.P$1
SOL_PWR_17: SOL_17.D (DRAIN), SOL_BANK_2.P$3 (PIN3), SOL_PWR_17.P$1
SOL_PWR_18: SOL_18.D (DRAIN), SOL_BANK_2.P$4 (PIN4), SOL_PWR_18.P$1
SOL_PWR_19: SOL_19.D (DRAIN), SOL_BANK_2.P$5 (PIN5), SOL_PWR_19.P$1
SOL_PWR_20: SOL_20.D (DRAIN), SOL_BANK_2.P$6 (PIN6), SOL_PWR_20.P$1
SOL_PWR_21: SOL_21.D (DRAIN), SOL_BANK_2.P$7 (PIN7), SOL_PWR_21.P$1
SOL_PWR_22: SOL_22.D (DRAIN), SOL_BANK_2.P$9 (PIN8), SOL_PWR_22.P$1
SOL_PWR_23: SOL_23.D (DRAIN), SOL_BANK_2.P$10 (PIN9), SOL_PWR_23.P$1
ST_BU: R38.1, R148.2, U11.14 (D3)
ST_BU_OUT: CABINET_I/O.P$4 (4), R148.1, ST_BU_OUT.P$1
ST_LI: CABINET_I/O.P$3 (3), ST_LI.D (COLLECTOR), ST_LI_.P$1
ST_LI_GATE: IC2.59 (SDA2/RA3), R116.2
SW_C_0: IC4.18 (Y1), SW_COL.P$10 (PIN9), SW_C_0.P$1
SW_C_1: IC4.3 (Y4), SW_COL.P$9 (PIN8), SW_C_1.P$1
SW_C_2: IC4.16 (Y2), SW_COL.P$8 (PIN7), SW_C_2.P$1
SW_C_3: IC4.5 (Y3), SW_COL.P$7 (PIN6), SW_C_3.P$1
SW_C_4: IC4.14 (Y3), SW_COL.P$6 (PIN5), SW_C_4.P$1
SW_C_5: IC4.7 (Y2), SW_COL.P$4 (PIN4), SW_C_5.P$1
SW_C_6: IC4.12 (Y4), SW_COL.P$3 (PIN3), SW_C_6.P$1
SW_C_7: IC4.9 (Y1), SW_COL.P$2 (PIN2), SW_C_7.P$1
SW_R_0: IC3.2 (A1), R82.1, SW_ROW.P$10 (PIN9), SW_R_0.P$1
SW_R_1: IC3.17 (A4), R81.1, SW_ROW.P$9 (PIN8), SW_R_1.P$1
SW_R_2: IC3.4 (A2), R80.1, SW_ROW.P$8 (PIN7), SW_R_2.P$1
SW_R_3: IC3.15 (A3), R79.1, SW_ROW.P$7 (PIN6), SW_R_3.P$1
SW_R_4: IC3.6 (A3), R78.2, SW_ROW.P$6 (PIN5), SW_R_4.P$1
SW_R_5: IC3.13 (A2), R77.2, SW_ROW.P$5 (PIN4), SW_R_5.P$1
SW_R_6: IC3.8 (A4), R76.2, SW_ROW.P$3 (PIN3), SW_R_6.P$1
SW_R_7: IC3.11 (A1), R75.2, SW_ROW.P$2 (PIN2), SW_R_7.P$1
S_L: AUDIO.2_A (T), AUDIO.2_B (T), R32.2, S_L.P$1
S_R: AUDIO.3_A (R), AUDIO.3_B (R), R34.2, S_R.P$1
TILT: R50.1, R149.2, U12.6 (D7)
TILT_OUT: CABINET_I/O.P$5 (5), R149.1, TILT_OUT.P$1
TX_PIC32: IC2.53 (SCL1A/SDO1A/U1ATX/RF8), PIC32_TC.P$3 (PIN3), PIC32_UART.5
TX_PROP: PROP_TC.P$3 (PIN3), PROP_UART.5, U1.37 (P30)
USBD+: IC2.57 (D+/RG2), USB_PROG.3
USBD-: IC2.56 (D-/RG3), USB_PROG.2
USER_0: R44.1, R154.2, U12.12 (D1)
USER_0_OUT: CABINET_I/O.P$10 (10), R154.1, USER_0_OUT.P$1
VUSB: IC2.54 (VBUS), USB_PROG.1
WATCHDOG: R135.1, U14.1 (A1), U14.4 (A2), U14.9 (A3), U14.12 (A4), U15.1 (A1), U15.4 (A2), U15.9 (A3), U15.12 (A4), U16.1 (A1), U16.4 (A2), U16.9 (A3), U16.12 (A4), U17.1 (A1), U17.4 (A2), U17.9 (A3), U17.12 (A4), U18.1 (A1), U18.4 (A2), U18.9 (A3), U18.12 (A4), U19.1 (A1), U19.4 (A2), U19.9 (A3), U19.12 (A4), U52.13 (1Q), WD.ANODE
WATCHDOG_ADJUST: C27.POS, D2.2 (ANODE), R134.1, U52.15 (1RXCX)
X0: U1.29 (X0), X2.P$1
X1: U1.28 (X1), X2.P$2

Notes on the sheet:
Reset
FQ7050B-8.000

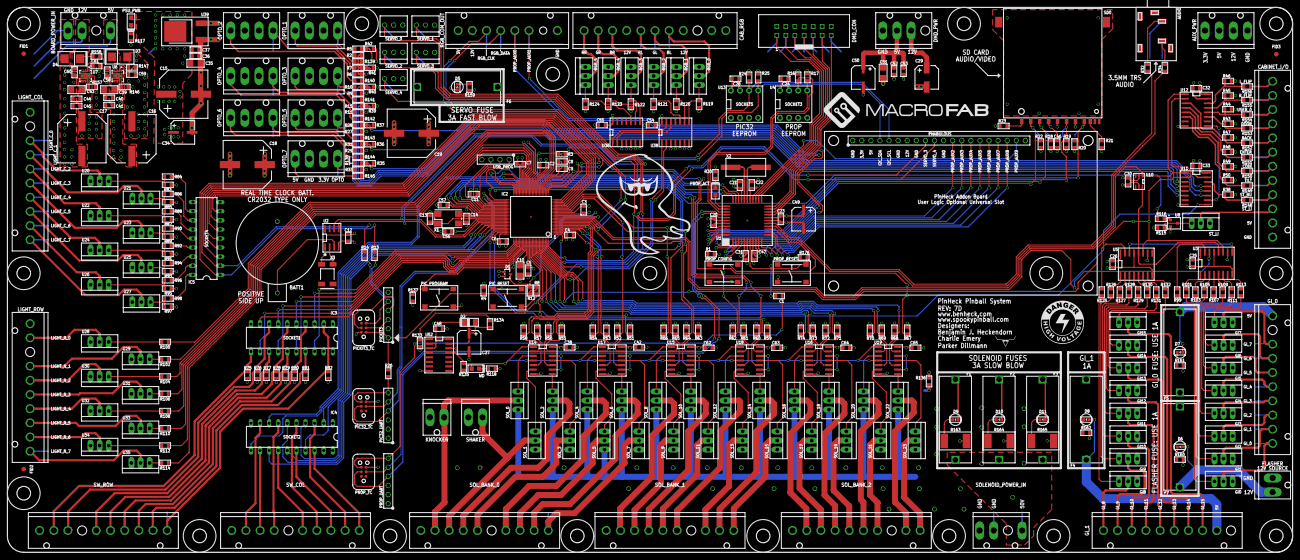
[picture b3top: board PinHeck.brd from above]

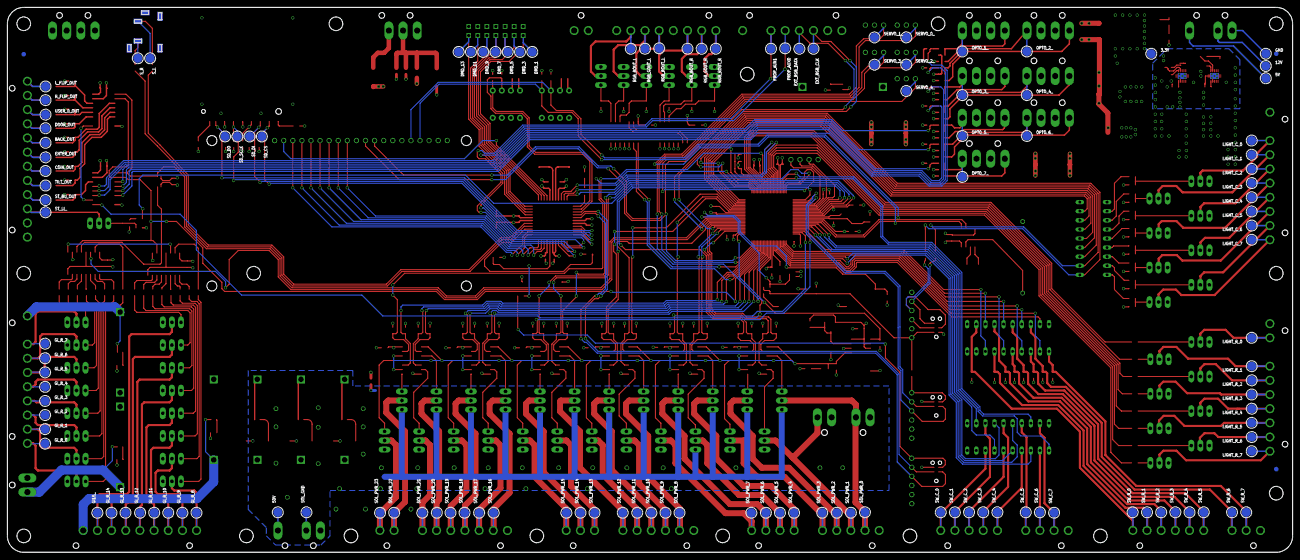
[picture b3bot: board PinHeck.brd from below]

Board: 6 copper layers, 359.2 x 152.3 mm, 545 parts (123 on the bottom side), 376 nets.

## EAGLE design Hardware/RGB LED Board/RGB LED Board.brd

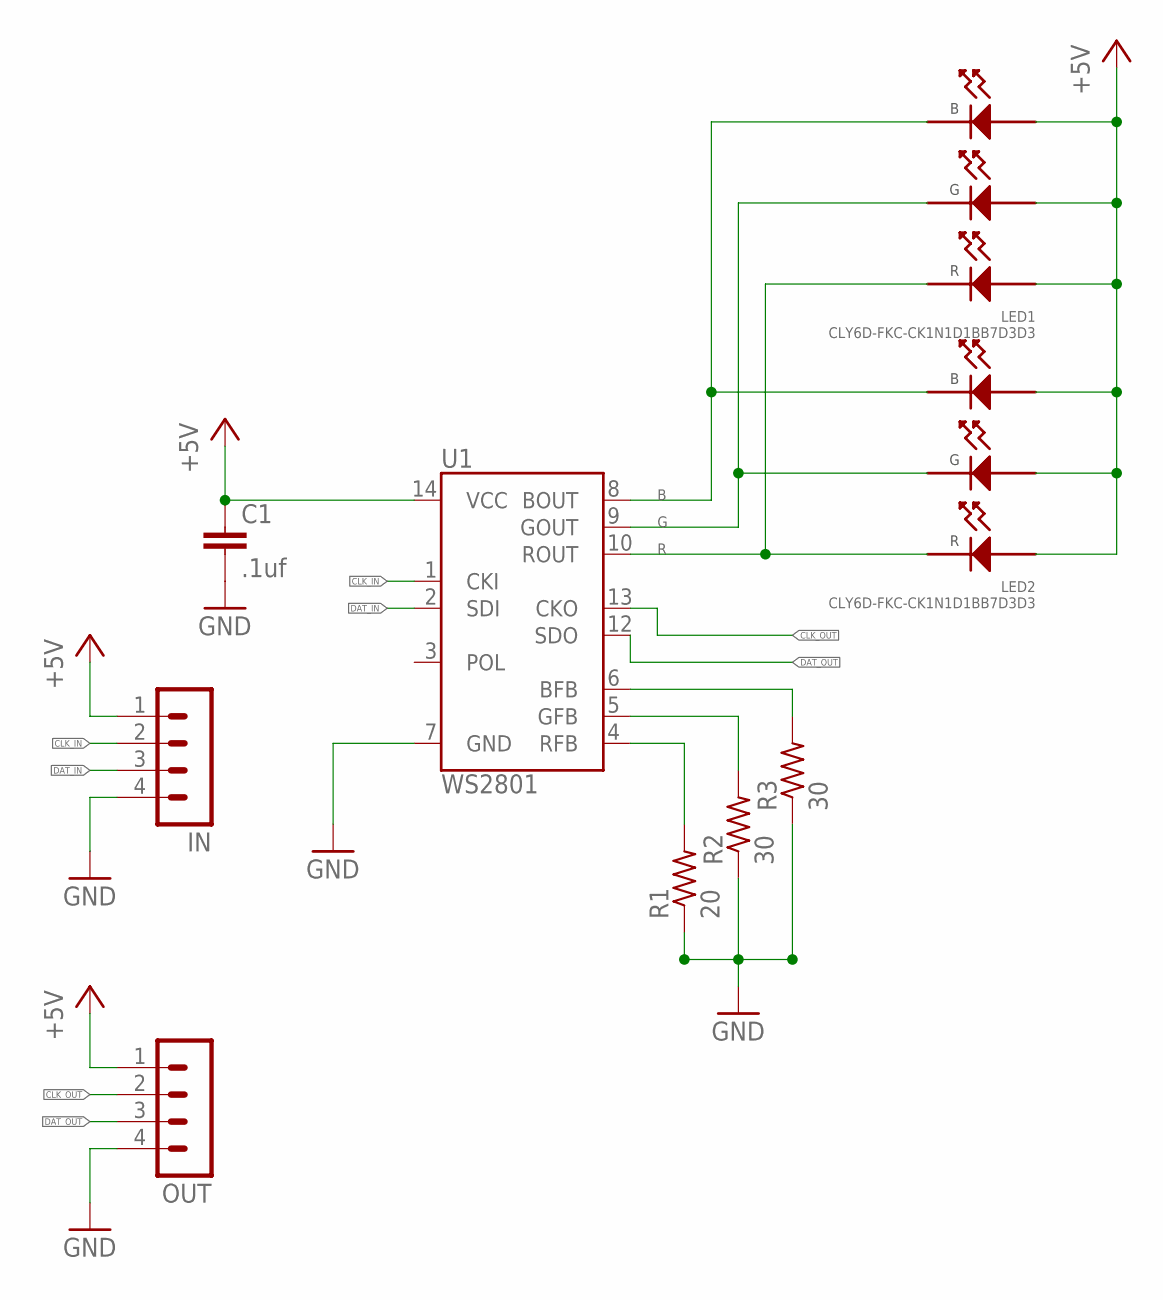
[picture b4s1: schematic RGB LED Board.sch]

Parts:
C1: .1uf; 0805
IN: MA04-1
LED1, LED2: CLY6D-FKC-CK1N1D1BB7D3D3; CLY6D-FKC
OUT: MA04-1
R1: 20; R0805
R2, R3: 30; R0805
U1: WS2801; SOP-14

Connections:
+5V: C1.1, IN.1, LED1.P$4 (ANODE_RED), LED1.P$5 (ANODE_GREEN), LED1.P$6 (ANODE_BLUE), LED2.P$4 (ANODE_RED), LED2.P$5 (ANODE_GREEN), LED2.P$6 (ANODE_BLUE), OUT.1, U1.14 (VCC)
B: LED1.P$1 (CATHODE_BLUE), LED2.P$1 (CATHODE_BLUE), U1.8 (BOUT)
BFB: R3.2, U1.6 (BFB)
CLK_IN: IN.2, U1.1 (CKI)
CLK_OUT: OUT.2, U1.13 (CKO)
DAT_IN: IN.3, U1.2 (SDI)
DAT_OUT: OUT.3, U1.12 (SDO)
G: LED1.P$2 (CATHODE_GREEN), LED2.P$2 (CATHODE_GREEN), U1.9 (GOUT)
GFB: R2.2, U1.5 (GFB)
GND: C1.2, IN.4, OUT.4, R1.1, R2.1, R3.1, U1.7 (GND)
R: LED1.P$3 (CATHODE_RED), LED2.P$3 (CATHODE_RED), U1.10 (ROUT)
RFB: R1.2, U1.4 (RFB)

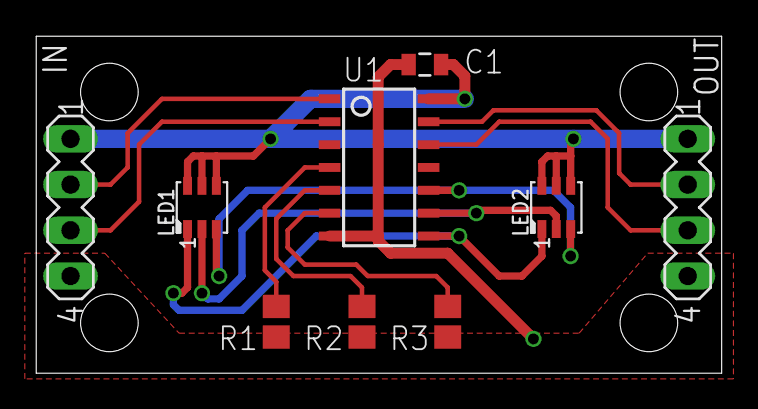
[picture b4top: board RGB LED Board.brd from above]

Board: 4 copper layers, 38.1 x 18.7 mm, 9 parts (0 on the bottom side), 12 nets.
